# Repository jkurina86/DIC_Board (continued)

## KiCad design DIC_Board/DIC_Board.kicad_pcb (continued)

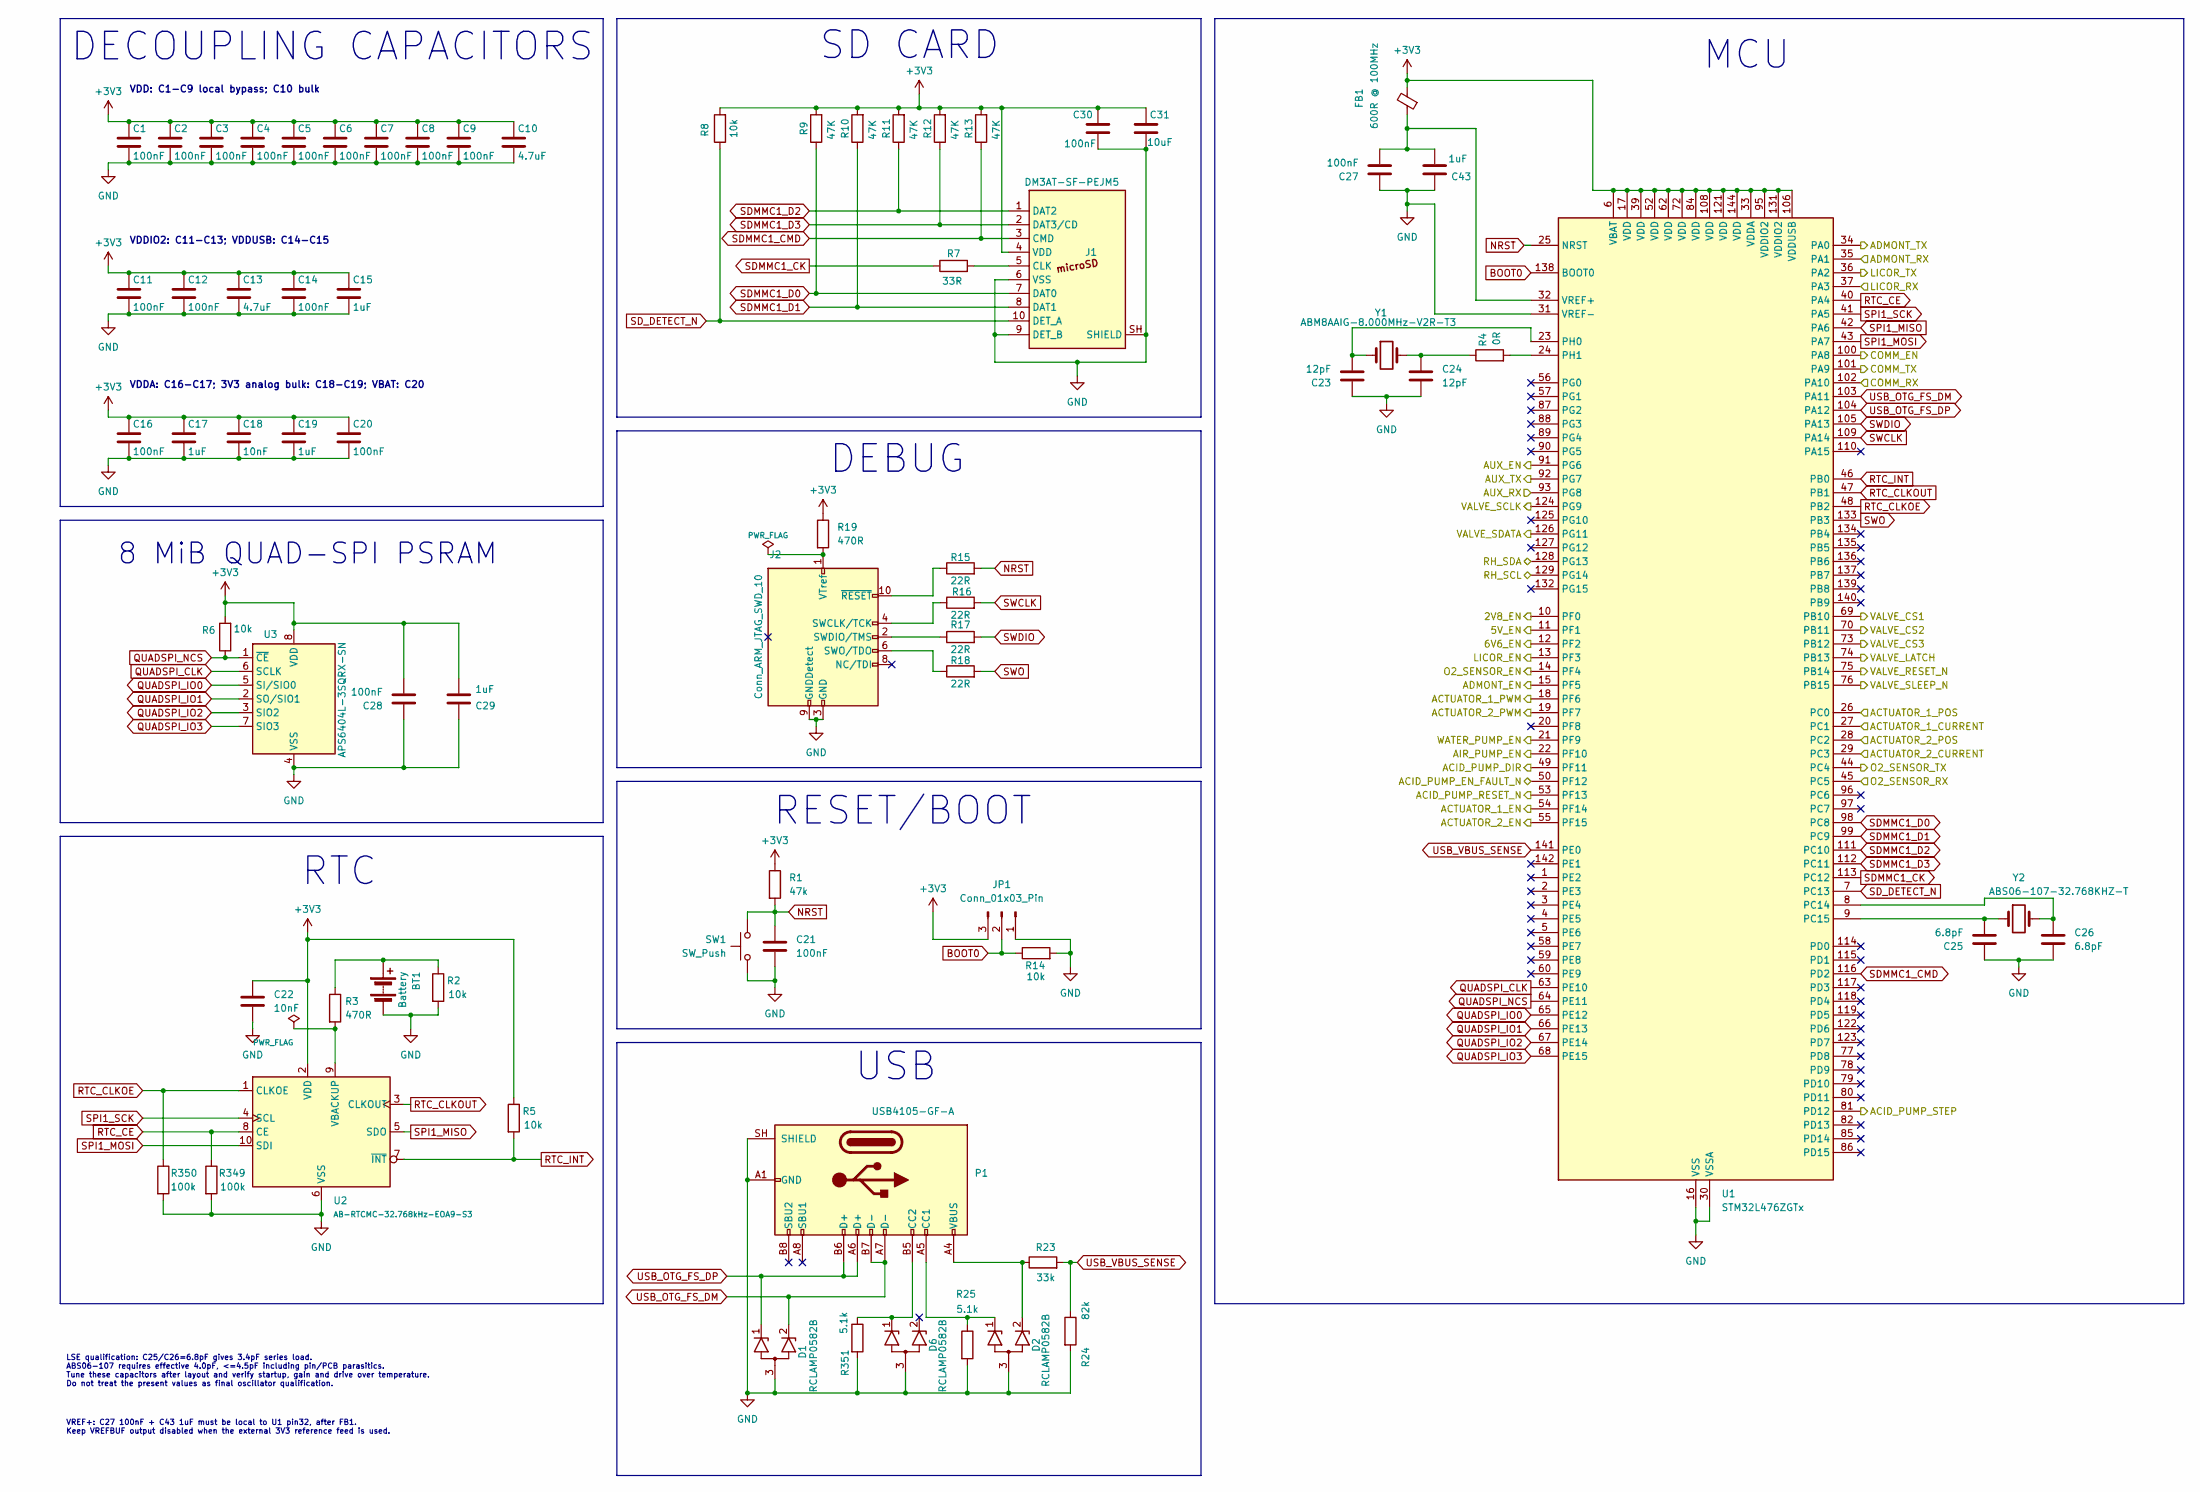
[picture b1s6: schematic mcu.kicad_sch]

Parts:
BT1: Battery; BatteryHolder_Keystone_3013_1x16mm; MPN 3013; DigiKey 36-3013-ND
C1, C2, C3, C4, C5, C6, C7, C8, C9, C11, C12, C14, C16, C20, C21, C27, C28, C30: 100nF; C_0603_1608Metric; Voltage Rating 50V; Tolerance 10%; MPN C1608X7R1H104K080AA
C10, C13: 4.7uF; C_0805_2012Metric; Voltage Rating 25V; Tolerance 10%; MPN C2012X7R1E475K125AB
C15, C17, C19, C29, C43: 1uF; C_0603_1608Metric; Voltage Rating 25V; Tolerance 10%; MPN C1608X7R1E105K080AB
C18, C22: 10nF; C_0603_1608Metric; Voltage Rating 50V; Tolerance 10%; MPN C1608X7R1H103K080AA
C23, C24: 12pF; C_0603_1608Metric; Voltage Rating 50V; Tolerance 5%; MPN C1608C0G1H120J080AA
C25, C26: 6.8pF; C_0402_1005Metric; Voltage Rating 50V; Tolerance 0.25pF; MPN GRM1555C1H6R8CA01D
C31: 10uF; C_0805_2012Metric; Voltage Rating 16V; Tolerance 10%; MPN C2012X7S1C106K125AC
D1, D2, D6: RCLAMP0582B; SOT-523; MPN RClamp0582B.TCT
FB1: 600R @ 100MHz; L_0603_1608Metric; Current Rating 500mA; MPN BLM18AG601SN1D
J1: DM3AT-SF-PEJM5; microSD_HC_Hirose_DM3AT-SF-PEJM5; MPN DM3AT-SF-PEJM5
J2: Conn_ARM_JTAG_SWD_10; Wurth_61201021621_2x05_P2.54mm_Vertical; MPN 61201021621; DigiKey 732-2094-ND
JP1: Conn_01x03_Pin; PinHeader_Wurth_61300311121_1x03_P2.54mm_Vertical; MPN 61300311121
P1: USB4105-GF-A; USB_C_Receptacle_GCT_USB4105-xx-A_16P_TopMnt_Horizontal; MPN USB4105-GF-A; DigiKey 2073-USB4105-GF-ACT-ND
R1: 47k; R_0603_1608Metric; Tolerance 1%; Power Rating 0.125W; MPN CRCW060347K0FKEA
R2, R5, R6, R8, R14: 10k; R_0603_1608Metric; Tolerance 1%; Power Rating 0.125W; MPN CRCW060310K0FKEA
R3, R19: 470R; R_0603_1608Metric; Tolerance 1%; Power Rating 0.125W; MPN CRCW0603470RFKEA
R4: 0R; R_0603_1608Metric; Tolerance Jumper; Power Rating 0.125W; MPN CRCW06030000Z0EA
R7: 33R; R_0603_1608Metric; Tolerance 1%; Power Rating 0.125W; MPN CRCW060333R0FKEA
R9, R10, R11, R12, R13: 47K; R_0603_1608Metric; Tolerance 1%; Power Rating 0.125W; MPN CRCW060347K0FKEA
R15, R16, R17, R18: 22R; R_0603_1608Metric; Tolerance 1%; Power Rating 0.125W; MPN CRCW060322R0FKEA
R23: 33k; R_0402_1005Metric; Tolerance 1%; Power Rating 0.1W; MPN CRCW040233K0FKED
R24: 82k; R_0402_1005Metric; Tolerance 1%; Power Rating 0.1W; MPN CRCW040282K0FKED
R25, R351: 5.1k; R_0402_1005Metric; Tolerance 1%; Power Rating 0.1W; MPN CRCW04025K10FKED
R349, R350: 100k; R_0603_1608Metric; Tolerance 1%; Power Rating 0.125W; MPN CRCW0603100KFKEA
SW1: SW_Push; SW_ESwitch_TL6330AF200Q; MPN TL6330AF200Q
U1: STM32L476ZGTx; LQFP-144_20x20mm_P0.5mm; MPN STM32L476ZGT6
U2: AB-RTCMC-32.768kHz-EOA9-S3; RTC_SMD_MicroCrystal_C3_2.5x3.7mm; MPN AB-RTCMC-32.768kHz-EOA9-S3
U3: APS6404L-3SQRX-SN; SOIC-8_3.9x4.9mm_P1.27mm; MPN APS6404L-3SQRX-SN; Mouser 878-APS6404L-3SQRXSN
Y1: ABM8AAIG-8.000MHz-V2R-T3; ABM8AAIG-2Pin_3.2x2.5mm; MPN ABM8AAIG-8.000MHz-V2R-T3
Y2: ABS06-107-32.768KHZ-T; ABS06-107-2Pin_2.0x1.2mm; MPN ABS06-107-32.768KHZ-T

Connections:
+3V3: C1.1, C2.1, C3.1, C4.1, C5.1, C6.1, C7.1, C8.1, C9.1, C10.1, C11.1, C12.1, C13.1, C14.1, C15.1, C16.1, C17.1, C18.1, C19.1, C20.1, C22.2, C28.1, C29.1, C30.1, C31.1, FB1.2, J1.4 (VDD), JP1.3, R1.1, R5.1, R6.2, R8.2, R9.2, R10.2, R11.2, R12.2, R13.2, R19.1, U1.6 (VBAT), U1.17 (VDD), U1.33 (VDDA), U1.39 (VDD), U1.52 (VDD), U1.62 (VDD), U1.72 (VDD), U1.84 (VDD), U1.95 (VDDIO2), U1.106 (VDDUSB), U1.108 (VDD), U1.121 (VDD), U1.131 (VDDIO2), U1.144 (VDD), U2.2 (VDD), U3.8 (VDD); also elsewhere on the board
/Actuators/ACTUATOR_1_CURRENT: U1.27 (PC1); also elsewhere on the board
/Actuators/ACTUATOR_1_EN: U1.54 (PF14); also elsewhere on the board
/Actuators/ACTUATOR_1_POS: U1.26 (PC0); also elsewhere on the board
/Actuators/ACTUATOR_1_PWM: U1.18 (PF6); also elsewhere on the board
/Actuators/ACTUATOR_2_CURRENT: U1.29 (PC3); also elsewhere on the board
/Actuators/ACTUATOR_2_EN: U1.55 (PF15); also elsewhere on the board
/Actuators/ACTUATOR_2_POS: U1.28 (PC2); also elsewhere on the board
/Actuators/ACTUATOR_2_PWM: U1.19 (PF7); also elsewhere on the board
/Comms/AUX_EN: U1.91 (PG6); also elsewhere on the board
/Comms/AUX_RX: U1.93 (PG8); also elsewhere on the board
/Comms/AUX_TX: U1.92 (PG7); also elsewhere on the board
/Comms/COMM_EN: U1.100 (PA8); also elsewhere on the board
/Comms/COMM_RX: U1.102 (PA10); also elsewhere on the board
/Comms/COMM_TX: U1.101 (PA9); also elsewhere on the board
/Power/2V8_EN: U1.10 (PF0); also elsewhere on the board
/Power/5V_EN: U1.11 (PF1); also elsewhere on the board
/Power/6V6_EN: U1.12 (PF2); also elsewhere on the board
/Pump Control/ACID_PUMP_DIR: U1.49 (PF11); also elsewhere on the board
/Pump Control/ACID_PUMP_EN_FAULT_N: U1.50 (PF12); also elsewhere on the board
/Pump Control/ACID_PUMP_RESET_N: U1.53 (PF13); also elsewhere on the board
/Pump Control/ACID_PUMP_STEP: U1.81 (PD12); also elsewhere on the board
/Pump Control/AIR_PUMP_EN: U1.22 (PF10); also elsewhere on the board
/Pump Control/WATER_PUMP_EN: U1.21 (PF9); also elsewhere on the board
/STM32 MCU/ADMONT_EN: U1.15 (PF5); also elsewhere on the board
/STM32 MCU/ADMONT_RX: U1.35 (PA1); also elsewhere on the board
/STM32 MCU/ADMONT_TX: U1.34 (PA0); also elsewhere on the board
/STM32 MCU/LICOR_EN: U1.13 (PF3); also elsewhere on the board
/STM32 MCU/LICOR_RX: U1.37 (PA3); also elsewhere on the board
/STM32 MCU/LICOR_TX: U1.36 (PA2); also elsewhere on the board
/STM32 MCU/O2_SENSOR_EN: U1.14 (PF4); also elsewhere on the board
/STM32 MCU/O2_SENSOR_RX: U1.45 (PC5); also elsewhere on the board
/STM32 MCU/O2_SENSOR_TX: U1.44 (PC4); also elsewhere on the board
/STM32 MCU/RH_SCL: U1.129 (PG14); also elsewhere on the board
/STM32 MCU/RH_SDA: U1.128 (PG13); also elsewhere on the board
/Valve Control/VALVE_CS1: U1.69 (PB10); also elsewhere on the board
/Valve Control/VALVE_CS2: U1.70 (PB11); also elsewhere on the board
/Valve Control/VALVE_CS3: U1.73 (PB12); also elsewhere on the board
/Valve Control/VALVE_LATCH: U1.74 (PB13); also elsewhere on the board
/Valve Control/VALVE_RESET_N: U1.75 (PB14); also elsewhere on the board
/Valve Control/VALVE_SCLK: U1.124 (PG9); also elsewhere on the board
/Valve Control/VALVE_SDATA: U1.126 (PG11); also elsewhere on the board
/Valve Control/VALVE_SLEEP_N: U1.76 (PB15); also elsewhere on the board
BOOT0: JP1.2, R14.1, U1.138 (BOOT0)
GND: BT1.2 (-), C1.2, C2.2, C3.2, C4.2, C5.2, C6.2, C7.2, C8.2, C9.2, C10.2, C11.2, C12.2, C13.2, C14.2, C15.2, C16.2, C17.2, C18.2, C19.2, C20.2, C21.1, C22.1, C23.2, C24.1, C25.2, C26.1, C27.2, C28.2, C29.2, C30.2, C31.2, C43.2, D1.3 (A), D2.3 (A), D6.3 (A), J1.6 (VSS), J1.9 (DET_B), J1.SH (SHIELD), J2.3 (GND), J2.5 (GND), J2.9 (GNDDetect), JP1.1, P1.A1 (GND), P1.A12 (GND), P1.B1 (GND), P1.B12 (GND), P1.SH (SHIELD), R2.2, R14.2, R24.2, R25.2, R349.2, R350.2, R351.2, SW1.2, U1.16 (VSS), U1.30 (VSSA), U1.31 (VREF-), U1.38 (VSS), U1.51 (VSS), U1.61 (VSS), U1.71 (VSS), U1.83 (VSS), U1.94 (VSS), U1.107 (VSS), U1.120 (VSS), U1.130 (VSS), U1.143 (VSS), U2.6 (VSS), U3.4 (VSS); also elsewhere on the board
NRST: C21.2, R1.2, R15.2, SW1.1, U1.25 (NRST)
unnamed: BT1.1 (+), R2.1, R3.1
unnamed: C24.2, R4.1, Y1.2
unnamed: D2.1 (K1), P1.A5 (CC1), R25.1
unnamed: D2.2 (K2), P1.A4 (VBUS), P1.A9 (VBUS), P1.B4 (VBUS), P1.B9 (VBUS), R23.1
unnamed: D6.1 (K1), P1.B5 (CC2), R351.1
unnamed: J1.5 (CLK), R7.2
unnamed: J2.4 (SWCLK/TCK), R16.1
unnamed: J2.2 (SWDIO/TMS), R17.1
unnamed: J2.6 (SWO/TDO), R18.1
unnamed: J2.1 (VTref), R19.2
unnamed: J2.10 (~RESET), R15.1
unnamed: C26.2, U1.8 (PC14), Y2.2
unnamed: C25.1, U1.9 (PC15), Y2.1
unnamed: C23.1, U1.23 (PH0), Y1.1
unnamed: R4.2, U1.24 (PH1)
unnamed: C27.1, C43.1, FB1.1, U1.32 (VREF+)
unnamed: R3.2, U2.9 (VBACKUP)
QUADSPI_CLK: U1.63 (PE10), U3.6 (SCLK)
QUADSPI_IO0: U1.65 (PE12), U3.5 (SI/SIO0)
QUADSPI_IO1: U1.66 (PE13), U3.2 (SO/SIO1)
QUADSPI_IO2: U1.67 (PE14), U3.3 (SIO2)
QUADSPI_IO3: U1.68 (PE15), U3.7 (SIO3)
QUADSPI_NCS: R6.1, U1.64 (PE11), U3.1 (~CE)
RTC_CE: R349.1, U1.40 (PA4), U2.8 (CE)
RTC_CLKOE: R350.1, U1.48 (PB2), U2.1 (CLKOE)
RTC_CLKOUT: U1.47 (PB1), U2.3 (CLKOUT)
RTC_INT: R5.2, U1.46 (PB0), U2.7 (~INT)
SDMMC1_CK: R7.1, U1.113 (PC12)
SDMMC1_CMD: J1.3 (CMD), R13.1, U1.116 (PD2)
SDMMC1_D0: J1.7 (DAT0), R9.1, U1.98 (PC8)
SDMMC1_D1: J1.8 (DAT1), R10.1, U1.99 (PC9)
SDMMC1_D2: J1.1 (DAT2), R11.1, U1.111 (PC10)
SDMMC1_D3: J1.2 (DAT3/CD), R12.1, U1.112 (PC11)
SD_DETECT_N: J1.10 (DET_A), R8.1, U1.7 (PC13)
SPI1_MISO: U1.42 (PA6), U2.5 (SDO)
SPI1_MOSI: U1.43 (PA7), U2.10 (SDI)
SPI1_SCK: U1.41 (PA5), U2.4 (SCL)
SWCLK: R16.2, U1.109 (PA14)
SWDIO: R17.2, U1.105 (PA13)
SWO: R18.2, U1.133 (PB3)
USB_OTG_FS_DM: D1.2 (K2), P1.A7 (D-), P1.B7 (D-), U1.103 (PA11)
USB_OTG_FS_DP: D1.1 (K1), P1.A6 (D+), P1.B6 (D+), U1.104 (PA12)
USB_VBUS_SENSE: R23.2, R24.1, U1.141 (PE0)

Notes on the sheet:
DECOUPLING CAPACITORS
RTC
USB
DEBUG
8 MiB QUAD-SPI PSRAM
VREF+: C27 100nF + C43 1uF must be local to U1 pin32, after FB1. Keep VREFBUF output disabled when the external 3V3 reference feed is used.
MCU
VDD: C1-C9 local bypass; C10 bulk
VDDIO2: C11-C13; VDDUSB: C14-C15
VDDA: C16-C17; 3V3 analog bulk: C18-C19; VBAT: C20
RESET/BOOT
SD CARD
LSE qualification: C25/C26=6.8pF gives 3.4pF series load. ABS06-107 requires effective 4.0pF, <=4.5pF including pin/PCB parasitics. Tune these capacitors after layout and verify startup, gain and drive over temperature. Do not treat the present values as final oscillator qualification.

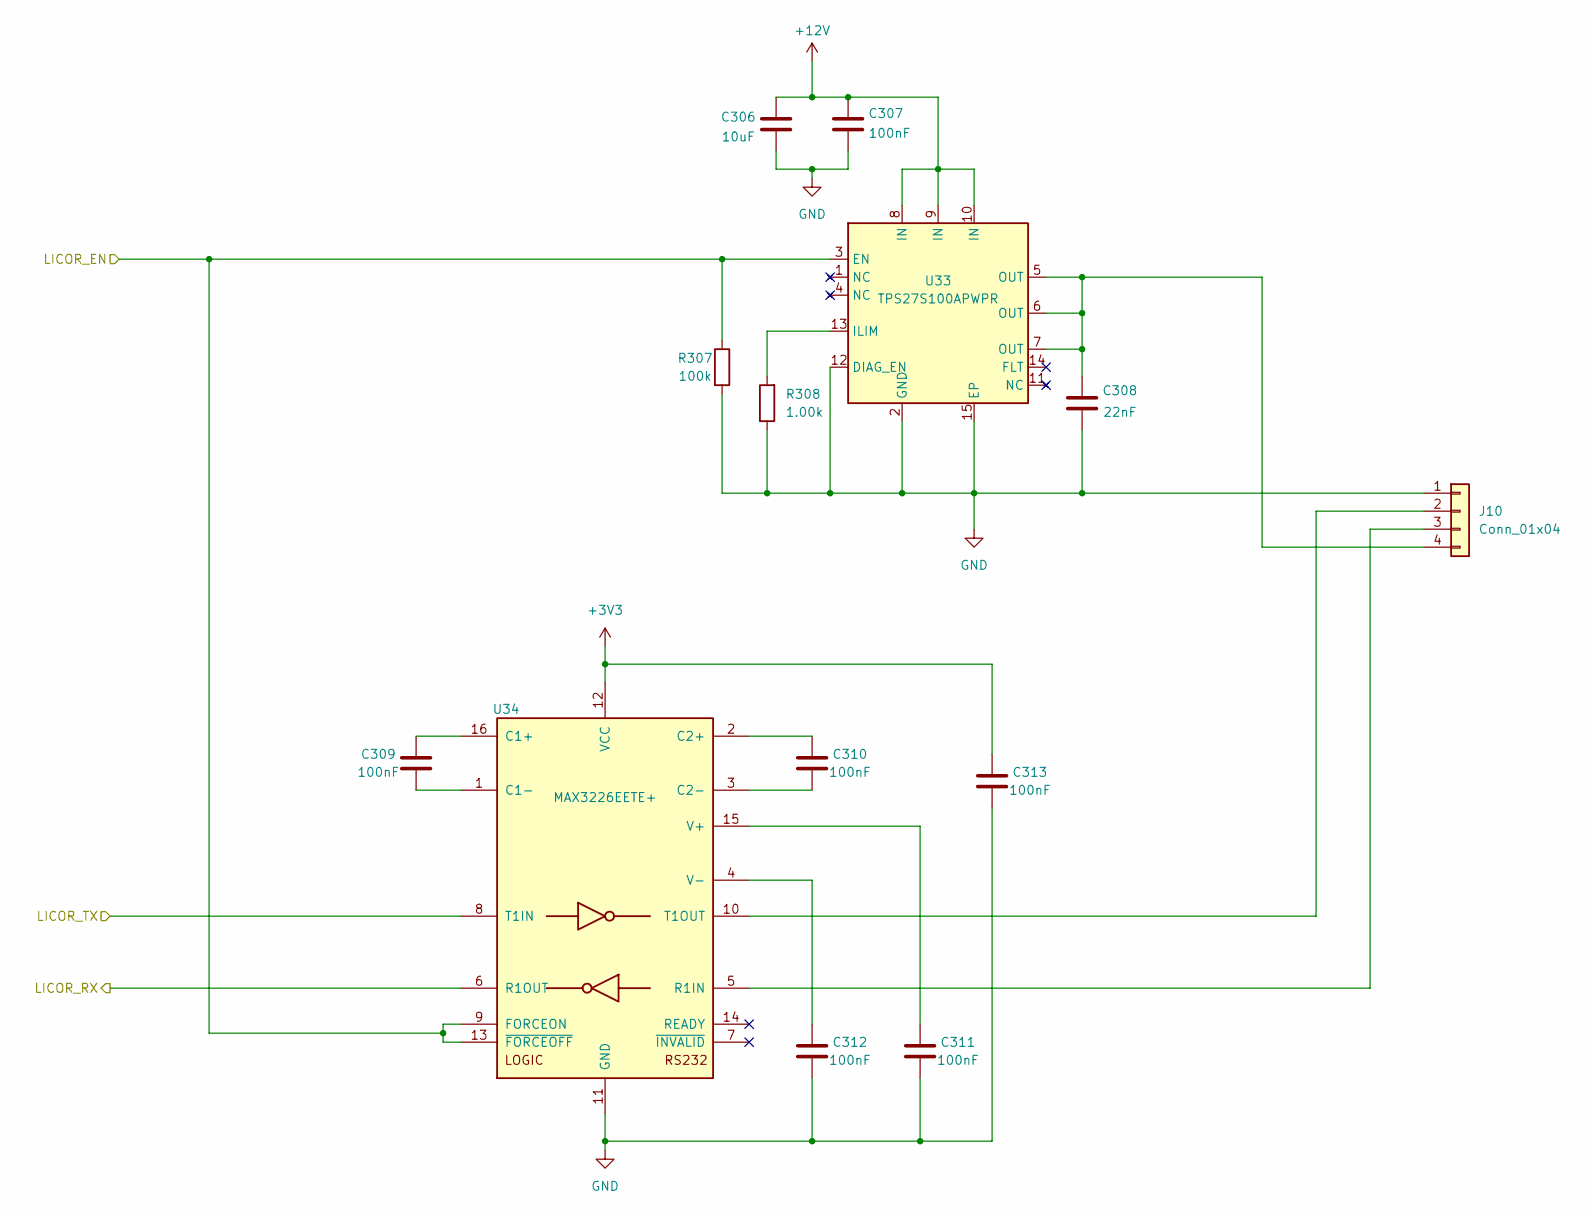
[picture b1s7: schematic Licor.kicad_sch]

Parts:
C306: 10uF; C_1206_3216Metric; MPN CGA5L1X7R1H106K160AC
C307, C309, C310, C311, C312, C313: 100nF; C_0402_1005Metric; MPN GRM155R71H104ME14D
C308: 22nF; C_0402_1005Metric; MPN GRM155R71H223KA12D
J10: Conn_01x04; Molex_Micro-Fit_3.0_43045-0400_2x02_P3.00mm_Horizontal; MPN 0430450400
R307: 100k; R_0402_1005Metric; MPN CRCW0402100KFKED
R308: 1.00k; R_0402_1005Metric; MPN CRCW04021K00FKED
U33: TPS27S100APWPR; TPS27S100_Thermal_Drill0p3; MPN TPS27S100APWPR; DigiKey 296-49002-1-ND
U34: MAX3226EETE+; TQFN-16-1EP_5x5mm_P0.8mm_EP3.1x3.1mm; MPN MAX3226EETE+

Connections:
+3V3: C313.1, U34.12 (VCC); also elsewhere on the board
+12V: C306.1, C307.1, U33.8 (IN), U33.9 (IN), U33.10 (IN); also elsewhere on the board
/STM32 MCU/LICOR_EN: R307.1, U33.3 (EN), U34.9 (FORCEON), U34.13 (~FORCEOFF); also elsewhere on the board
/STM32 MCU/LICOR_RX: U34.6 (R1OUT); also elsewhere on the board
/STM32 MCU/LICOR_TX: U34.8 (T1IN); also elsewhere on the board
GND: C306.2, C307.2, C308.2, C311.2, C312.2, C313.2, J10.1, R307.2, R308.1, U33.2 (GND), U33.12 (DIAG_EN), U33.15 (EP), U34.11 (GND), U34.17 (EP); also elsewhere on the board
unnamed: J10.2, U34.10 (T1OUT)
unnamed: J10.3, U34.5 (R1IN)
unnamed: C308.1, J10.4, U33.5 (OUT), U33.6 (OUT), U33.7 (OUT)
unnamed: R308.2, U33.13 (ILIM)
unnamed: C309.1, U34.16 (C1+)
unnamed: C309.2, U34.1 (C1-)
unnamed: C310.1, U34.2 (C2+)
unnamed: C310.2, U34.3 (C2-)
unnamed: C311.1, U34.15 (V+)
unnamed: C312.1, U34.4 (V-)

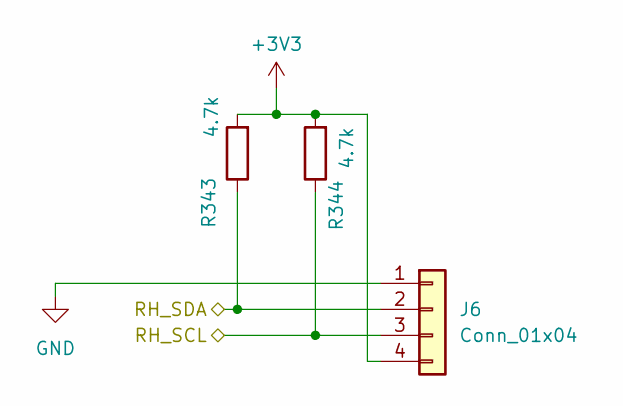
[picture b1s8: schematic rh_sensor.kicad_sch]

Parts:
J6: Conn_01x04; Molex_Micro-Fit_3.0_43045-0400_2x02_P3.00mm_Horizontal; MPN 0430450400
R343, R344: 4.7k; R_0603_1608Metric; Tolerance 1%; Power Rating 0.125W; MPN CRCW06034K70FKEA

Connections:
+3V3: J6.4, R343.2, R344.2; also elsewhere on the board
/STM32 MCU/RH_SCL: J6.3, R344.1; also elsewhere on the board
/STM32 MCU/RH_SDA: J6.2, R343.1; also elsewhere on the board
GND: J6.1; also elsewhere on the board

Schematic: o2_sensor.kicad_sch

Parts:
C328: 10uF; C_1206_3216Metric; MPN CGA5L1X7R1H106K160AC
C329: 100nF; C_0402_1005Metric; MPN GRM155R71H104ME14D
C330: 22nF; C_0402_1005Metric; MPN GRM155R71H223KA12D
J7: Conn_01x04; Molex_Micro-Fit_3.0_43045-0400_2x02_P3.00mm_Horizontal; MPN 0430450400
R340: 15k; R_0402_1005Metric; MPN CRCW040215K0FKED
R341: 100k; R_0402_1005Metric; MPN CRCW0402100KFKED
R342: 1.00k; R_0402_1005Metric; MPN CRCW04021K00FKED
U38: TPS27S100APWPR; TPS27S100_Thermal_Drill0p3; MPN TPS27S100APWPR; DigiKey 296-49002-1-ND

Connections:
+5V: C328.1, C329.1, U38.8 (IN), U38.9 (IN), U38.10 (IN); also elsewhere on the board
/STM32 MCU/O2_SENSOR_EN: R340.1; also elsewhere on the board
/STM32 MCU/O2_SENSOR_RX: J7.3; also elsewhere on the board
/STM32 MCU/O2_SENSOR_TX: J7.2; also elsewhere on the board
GND: C328.2, C329.2, C330.2, J7.1, R341.2, R342.1, U38.2 (GND), U38.12 (DIAG_EN), U38.15 (EP); also elsewhere on the board
unnamed: C330.1, J7.4, U38.5 (OUT), U38.6 (OUT), U38.7 (OUT)
unnamed: R340.2, R341.1, U38.3 (EN)
unnamed: R342.2, U38.13 (ILIM)

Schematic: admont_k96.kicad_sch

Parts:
C314: 10uF; C_1206_3216Metric; MPN CGA5L1X7R1H106K160AC
C315: 100nF; C_0402_1005Metric; MPN GRM155R71H104ME14D
C316: 22nF; C_0402_1005Metric; MPN GRM155R71H223KA12D
J8: Conn_01x04; Molex_Micro-Fit_3.0_43045-0400_2x02_P3.00mm_Horizontal; MPN 0430450400
R309: 15k; R_0402_1005Metric; MPN CRCW040215K0FKED
R310: 100k; R_0402_1005Metric; MPN CRCW0402100KFKED
R311: 1.00k; R_0402_1005Metric; MPN CRCW04021K00FKED
U35: TPS27S100APWPR; TPS27S100_Thermal_Drill0p3; MPN TPS27S100APWPR; DigiKey 296-49002-1-ND

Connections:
+6V6: C314.1, C315.1, U35.8 (IN), U35.9 (IN), U35.10 (IN); also elsewhere on the board
/STM32 MCU/ADMONT_EN: R309.1; also elsewhere on the board
/STM32 MCU/ADMONT_RX: J8.3; also elsewhere on the board
/STM32 MCU/ADMONT_TX: J8.2; also elsewhere on the board
GND: C314.2, C315.2, C316.2, J8.1, R310.2, R311.1, U35.2 (GND), U35.12 (DIAG_EN), U35.15 (EP); also elsewhere on the board
unnamed: C316.1, J8.4, U35.5 (OUT), U35.6 (OUT), U35.7 (OUT)
unnamed: R309.2, R310.1, U35.3 (EN)
unnamed: R311.2, U35.13 (ILIM)

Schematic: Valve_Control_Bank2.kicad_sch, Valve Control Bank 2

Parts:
C210: 0.47uF; C_0603_1608Metric_Pad1.08x0.95mm_HandSolder; MPN CGA3E3X7R1H474K080AE
C211: 0.01uF; C_0603_1608Metric_Pad1.08x0.95mm_HandSolder; MPN C0603C103K2RACTU
C212, C213: 0.1uF; C_0603_1608Metric_Pad1.08x0.95mm_HandSolder; MPN C0603X104K5RAC7867
C214: 100uF; CP_Radial_D8.0mm_P3.50mm; MPN UHE1H101MPD
R332, R333, R334, R335: 3.3R; R_0402_1005Metric; Tolerance 1%; Power Rating 0.2W; MPN CRCW04023R30FKEDHP
U21: DRV8823QDCARQ1; DRV8823_DCA48_ReviewFixed; MPN DRV8823QDCARQ1

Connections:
+12V: C212.1, C213.2, C214.1, U21.1 (VM1), U21.2 (VM2), U21.23 (VM3), U21.24 (VM4); also elsewhere on the board
/Valve Control/VALVE_CS2: U21.45 (SCS); also elsewhere on the board
/Valve Control/VALVE_LATCH: U21.30 (SSTB); also elsewhere on the board
/Valve Control/VALVE_RESET_N: U21.43 (RESETn); also elsewhere on the board
/Valve Control/VALVE_SCLK: U21.33 (SCLK); also elsewhere on the board
/Valve Control/VALVE_SDATA: U21.31 (SDATA); also elsewhere on the board
/Valve Control/VALVE_SLEEP_N: U21.42 (SLEEPn); also elsewhere on the board
/Valve Control/Valve Control Bank 2/VALVE5_A: U21.5 (AOUT1); also elsewhere on the board
/Valve Control/Valve Control Bank 2/VALVE5_B: U21.3 (AOUT2); also elsewhere on the board
/Valve Control/Valve Control Bank 2/VALVE6_A: U21.48 (BOUT1); also elsewhere on the board
/Valve Control/Valve Control Bank 2/VALVE6_B: U21.46 (BOUT2); also elsewhere on the board
/Valve Control/Valve Control Bank 2/VALVE7_A: U21.27 (COUT1); also elsewhere on the board
/Valve Control/Valve Control Bank 2/VALVE7_B: U21.25 (COUT2); also elsewhere on the board
/Valve Control/Valve Control Bank 2/VALVE8_A: U21.22 (DOUT1); also elsewhere on the board
/Valve Control/Valve Control Bank 2/VALVE8_B: U21.20 (DOUT2); also elsewhere on the board
/Valve Control/Valve Control Bank 2/VREF1: C210.2, U21.16 (V3P3), U21.17 (ABVREF), U21.18 (CDVREF)
GND: C210.1, C213.1, C214.2, R332.2, R333.2, R334.2, R335.2, U21.10 (PGND), U21.11 (PGND), U21.12 (PGND), U21.13 (PGND), U21.14 (PGND), U21.15 (PGND), U21.34 (PGND), U21.35 (PGND), U21.36 (PGND), U21.37 (PGND), U21.38 (PGND), U21.39 (PGND), U21.49 (EPAD); also elsewhere on the board
unnamed: R332.1, U21.4 (AISEN)
unnamed: R333.1, U21.47 (BISEN)
unnamed: R334.1, U21.26 (CISEN)
unnamed: C211.2, U21.7 (CP1)
unnamed: C211.1, U21.8 (CP2)
unnamed: R335.1, U21.21 (DISEN)
unnamed: C212.2, U21.9 (VCP)

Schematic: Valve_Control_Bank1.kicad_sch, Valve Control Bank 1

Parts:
C200: 0.47uF; C_0603_1608Metric_Pad1.08x0.95mm_HandSolder; MPN CGA3E3X7R1H474K080AE
C201: 0.01uF; C_0603_1608Metric_Pad1.08x0.95mm_HandSolder; MPN C0603C103K2RACTU
C202, C203: 0.1uF; C_0603_1608Metric_Pad1.08x0.95mm_HandSolder; MPN C0603X104K5RAC7867
C204: 100uF; CP_Radial_D8.0mm_P3.50mm; MPN UHE1H101MPD
R318, R319, R330, R331: 3.3R; R_0402_1005Metric; Tolerance 1%; Power Rating 0.2W; MPN CRCW04023R30FKEDHP
U20: DRV8823QDCARQ1; DRV8823_DCA48_ReviewFixed; MPN DRV8823QDCARQ1

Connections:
+12V: C202.1, C203.2, C204.1, U20.1 (VM1), U20.2 (VM2), U20.23 (VM3), U20.24 (VM4); also elsewhere on the board
/Valve Control/VALVE_CS1: U20.45 (SCS); also elsewhere on the board
/Valve Control/VALVE_LATCH: U20.30 (SSTB); also elsewhere on the board
/Valve Control/VALVE_RESET_N: U20.43 (RESETn); also elsewhere on the board
/Valve Control/VALVE_SCLK: U20.33 (SCLK); also elsewhere on the board
/Valve Control/VALVE_SDATA: U20.31 (SDATA); also elsewhere on the board
/Valve Control/VALVE_SLEEP_N: U20.42 (SLEEPn); also elsewhere on the board
/Valve Control/Valve Control Bank 1/VALVE1_A: U20.5 (AOUT1); also elsewhere on the board
/Valve Control/Valve Control Bank 1/VALVE1_B: U20.3 (AOUT2); also elsewhere on the board
/Valve Control/Valve Control Bank 1/VALVE2_A: U20.48 (BOUT1); also elsewhere on the board
/Valve Control/Valve Control Bank 1/VALVE2_B: U20.46 (BOUT2); also elsewhere on the board
/Valve Control/Valve Control Bank 1/VALVE3_A: U20.27 (COUT1); also elsewhere on the board
/Valve Control/Valve Control Bank 1/VALVE3_B: U20.25 (COUT2); also elsewhere on the board
/Valve Control/Valve Control Bank 1/VALVE4_A: U20.22 (DOUT1); also elsewhere on the board
/Valve Control/Valve Control Bank 1/VALVE4_B: U20.20 (DOUT2); also elsewhere on the board
/Valve Control/Valve Control Bank 1/VREF1: C200.2, U20.16 (V3P3), U20.17 (ABVREF), U20.18 (CDVREF)
GND: C200.1, C203.1, C204.2, R318.2, R319.2, R330.2, R331.2, U20.10 (PGND), U20.11 (PGND), U20.12 (PGND), U20.13 (PGND), U20.14 (PGND), U20.15 (PGND), U20.34 (PGND), U20.35 (PGND), U20.36 (PGND), U20.37 (PGND), U20.38 (PGND), U20.39 (PGND), U20.49 (EPAD); also elsewhere on the board
unnamed: R318.1, U20.4 (AISEN)
unnamed: R319.1, U20.47 (BISEN)
unnamed: R330.1, U20.26 (CISEN)
unnamed: C201.2, U20.7 (CP1)
unnamed: C201.1, U20.8 (CP2)
unnamed: R331.1, U20.21 (DISEN)
unnamed: C202.2, U20.9 (VCP)

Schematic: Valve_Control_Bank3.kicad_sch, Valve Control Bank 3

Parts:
C220: 0.47uF; C_0603_1608Metric_Pad1.08x0.95mm_HandSolder; MPN CGA3E3X7R1H474K080AE
C221: 0.01uF; C_0603_1608Metric_Pad1.08x0.95mm_HandSolder; MPN C0603C103K2RACTU
C222, C223: 0.1uF; C_0603_1608Metric_Pad1.08x0.95mm_HandSolder; MPN C0603X104K5RAC7867
C224: 100uF; CP_Radial_D8.0mm_P3.50mm; MPN UHE1H101MPD
R336, R337, R338, R339: 3.3R; R_0402_1005Metric; Tolerance 1%; Power Rating 0.2W; MPN CRCW04023R30FKEDHP
U22: DRV8823QDCARQ1; DRV8823_DCA48_ReviewFixed; MPN DRV8823QDCARQ1

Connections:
+12V: C222.1, C223.2, C224.1, U22.1 (VM1), U22.2 (VM2), U22.23 (VM3), U22.24 (VM4); also elsewhere on the board
/Valve Control/VALVE_CS3: U22.45 (SCS); also elsewhere on the board
/Valve Control/VALVE_LATCH: U22.30 (SSTB); also elsewhere on the board
/Valve Control/VALVE_RESET_N: U22.43 (RESETn); also elsewhere on the board
/Valve Control/VALVE_SCLK: U22.33 (SCLK); also elsewhere on the board
/Valve Control/VALVE_SDATA: U22.31 (SDATA); also elsewhere on the board
/Valve Control/VALVE_SLEEP_N: U22.42 (SLEEPn); also elsewhere on the board
/Valve Control/Valve Control Bank 3/VALVE9_A: U22.5 (AOUT1); also elsewhere on the board
/Valve Control/Valve Control Bank 3/VALVE9_B: U22.3 (AOUT2); also elsewhere on the board
/Valve Control/Valve Control Bank 3/VALVE10_A: U22.48 (BOUT1); also elsewhere on the board
/Valve Control/Valve Control Bank 3/VALVE10_B: U22.46 (BOUT2); also elsewhere on the board
/Valve Control/Valve Control Bank 3/VALVE11_A: U22.27 (COUT1); also elsewhere on the board
/Valve Control/Valve Control Bank 3/VALVE11_B: U22.25 (COUT2); also elsewhere on the board
/Valve Control/Valve Control Bank 3/VALVE12_A: U22.22 (DOUT1); also elsewhere on the board
/Valve Control/Valve Control Bank 3/VALVE12_B: U22.20 (DOUT2); also elsewhere on the board
/Valve Control/Valve Control Bank 3/VREF1: C220.2, U22.16 (V3P3), U22.17 (ABVREF), U22.18 (CDVREF)
GND: C220.1, C223.1, C224.2, R336.2, R337.2, R338.2, R339.2, U22.10 (PGND), U22.11 (PGND), U22.12 (PGND), U22.13 (PGND), U22.14 (PGND), U22.15 (PGND), U22.34 (PGND), U22.35 (PGND), U22.36 (PGND), U22.37 (PGND), U22.38 (PGND), U22.39 (PGND), U22.49 (EPAD); also elsewhere on the board
unnamed: R336.1, U22.4 (AISEN)
unnamed: R337.1, U22.47 (BISEN)
unnamed: R338.1, U22.26 (CISEN)
unnamed: C221.2, U22.7 (CP1)
unnamed: C221.1, U22.8 (CP2)
unnamed: R339.1, U22.21 (DISEN)
unnamed: C222.2, U22.9 (VCP)

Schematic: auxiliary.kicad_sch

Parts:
C332, C338, C339, C341, C342: 100nF; C_0402_1005Metric; MPN GRM155R71H104ME14D
D5: BZT52C8V2-7-F; D_SOD-123; MPN BZT52C8V2-7-F
J12: Conn_01x04; Molex_Micro-Fit_3.0_43045-0400_2x02_P3.00mm_Horizontal; MPN 0430450400
J13: Conn_01x05_Pin; PinHeader_Wurth_61300511121_1x05_P2.54mm_Vertical; MPN 61300511121
Q1: AO4630; SOIC-8_3.9x4.9mm_P1.27mm; Manufacturer_Part_Number AO4630
R345, R346: 100k; R_0402_1005Metric; MPN CRCW0402100KFKED
R347: 4.7k; R_0402_1005Metric; MPN CRCW04024K70FKED
U40: MAX3226EETE+; TQFN-16-1EP_5x5mm_P0.8mm_EP3.1x3.1mm; MPN MAX3226EETE+

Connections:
+3V3: C342.1, J13.1, U40.12 (VCC); also elsewhere on the board
+5V: J13.3; also elsewhere on the board
+12V: J13.5; also elsewhere on the board
/Comms/AUX_EN: Q1.2 (G1), R346.2, U40.9 (FORCEON), U40.13 (~FORCEOFF); also elsewhere on the board
/Comms/AUX_RX: U40.6 (R1OUT); also elsewhere on the board
/Comms/AUX_TX: U40.8 (T1IN); also elsewhere on the board
GND: C339.2, C341.2, C342.2, J12.1, Q1.1 (S1), R346.1, U40.11 (GND), U40.17 (EP); also elsewhere on the board
unnamed: D5.2 (A), Q1.4 (G2), R345.1, R347.1
unnamed: D5.1 (K), J13.2, J13.4, Q1.3 (S2), R345.2
unnamed: J12.2, U40.10 (T1OUT)
unnamed: J12.3, U40.5 (R1IN)
unnamed: J12.4, Q1.5 (D2_1), Q1.6 (D2_2)
unnamed: Q1.7 (D1_1), Q1.8 (D1_2), R347.2
unnamed: C332.1, U40.16 (C1+)
unnamed: C332.2, U40.1 (C1-)
unnamed: C338.1, U40.2 (C2+)
unnamed: C338.2, U40.3 (C2-)
unnamed: C341.1, U40.15 (V+)
unnamed: C339.1, U40.4 (V-)

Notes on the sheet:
AUX_EN: high = load power and RS-232 TX enabled. Wait for peripheral startup before transmitting. U40 exposed pad 17 is connected to GND.

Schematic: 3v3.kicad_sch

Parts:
C34, C35: 0.1uF; C_0603_1608Metric; Voltage Rating 50V; Tolerance 10%; MPN C1608X7R1H104K080AA
C115, C116: 10uF; C_1206_3216Metric; MPN CGA5L1X7R1H106K160AC
C117, C118: 47uF; C_1210_3225Metric; MPN GRM32ER61A476ME20L
C901: 180uF 16V; CP_Elec_6.3x5.9; Voltage Rating 16V; Tolerance 20%; MPN 16SVPF180M
R109: 10k; R_0402_1005Metric; MPN CRCW040210K0FKED
R110: 4.32k; R_0402_1005Metric; MPN CRCW04024K32FKED
TP23: +3V3; TestPoint_Pad_D1.0mm
U11: TPSM53603RDAR; Texas_B3QFN-14-1EP_5x5.5mm_P0.65mm_ThermalVia; MPN TPSM53603RDAR

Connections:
+3V3: C34.1, C117.1, C118.1, C901.1, R109.1, TP23.1 (1_1), U11.7 (VOUT), U11.8 (VOUT); also elsewhere on the board
/Power/12V/P_IN: C35.1, C115.1, C116.1, U11.1 (VIN), U11.2 (EN), U11.14 (VIN); also elsewhere on the board
GND: C34.2, C35.2, C115.2, C116.2, C117.2, C118.2, C901.2, R110.2, U11.3 (NC/PGND), U11.10 (NC/PGND), U11.11 (NC/PGND), U11.12 (AGND), U11.15 (PGND); also elsewhere on the board
unnamed: R109.2, R110.1, U11.9 (FB)

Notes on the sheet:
Output bulk
REGULATED +3V3 / 3 A

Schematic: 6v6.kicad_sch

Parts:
C32, C33: 0.1uF; C_0603_1608Metric; Voltage Rating 50V; Tolerance 10%; MPN C1608X7R1H104K080AA
C126, C127: 10uF; C_1206_3216Metric; MPN CGA5L1X7R1H106K160AC
C128, C129: 47uF; C_1210_3225Metric; MPN GRM32ER61A476ME20L
C903: 180uF 16V; CP_Elec_6.3x5.9; Voltage Rating 16V; Tolerance 20%; MPN 16SVPF180M
R22: 100k; R_0402_1005Metric; MPN CRCW0402100KFKED
R119: 10k; R_0402_1005Metric; MPN CRCW040210K0FKED
R120: 1.78k; R_0402_1005Metric; MPN CRCW04021K78FKED
TP25: +6V6; TestPoint_Pad_D1.0mm
U13: TPSM53603RDAR; Texas_B3QFN-14-1EP_5x5.5mm_P0.65mm_ThermalVia; MPN TPSM53603RDAR

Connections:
+6V6: C33.1, C128.1, C129.1, C903.1, R119.1, TP25.1 (1_1), U13.7 (VOUT), U13.8 (VOUT); also elsewhere on the board
+12V: C32.1, C126.1, C127.1, U13.1 (VIN), U13.14 (VIN); also elsewhere on the board
/Power/6V6_EN: R22.1, U13.2 (EN); also elsewhere on the board
GND: C32.2, C33.2, C126.2, C127.2, C128.2, C129.2, C903.2, R22.2, R120.2, U13.3 (NC/PGND), U13.10 (NC/PGND), U13.11 (NC/PGND), U13.12 (AGND), U13.15 (PGND); also elsewhere on the board
unnamed: R119.2, R120.1, U13.9 (FB)

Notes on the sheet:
REGULATED +6V6 / 3 A
Output bulk

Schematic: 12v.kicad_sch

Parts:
C40, C42: 0.1uF; C_0603_1608Metric; Voltage Rating 50V; Tolerance 10%; MPN C1608X7R1H104K080AA
C41: 100uF; CP_Elec_8x10.5; Voltage Rating 35V; MPN EEHZA1V101P
C102, C103: 100nF; C_0402_1005Metric; MPN GRM155R71H104ME14D
C104: 100nF; C_0603_1608Metric; Tolerance 10%; Voltage Rating 50V; MPN C1608X7R1H104K080AA
C105: 1nF; C_0603_1608Metric; Tolerance 5%; Voltage Rating 50V; MPN C1608C0G1H102J080AA
C106: 10uF; C_1206_3216Metric; MPN GRM31CR71E106KA12L
C107, C108: 10uF; C_1206_3216Metric; MPN CGA5L1X7R1H106K160AC
C109, C110, C111, C112: 22uF; C_1210_3225Metric; Voltage Rating 25V; Tolerance 20%; MPN GRM32ER71E226ME15L
C113: 220uF; CP_Elec_8x10.5; MPN EEHZA1E221P
C119: 10nF; C_0402_1005Metric; Voltage Rating 50V; Tolerance 10%; MPN CGA2B3X7R1H103K050BB
L10: 4.7uH; L_Coilcraft_XAL1010-XXX; MPN XAL1010-472MEB
R100: 150k; R_0402_1005Metric; MPN CRCW0402150KFKED
R101: 24.9k; R_0402_1005Metric; MPN CRCW040224K9FKED
R102: 49.9k; R_0402_1005Metric; MPN CRCW040249K9FKED
R103: 10m; R_2512_6332Metric; Power Rating 1W; Tolerance 1%; MPN WSL2512R0100FEA
R104: 100k; R_0402_1005Metric; MPN CRCW0402100KFKED
R105: 11.1k; R_0402_1005Metric; MPN CRCW040211K1FKED
R106: 10k; R_0402_1005Metric; Tolerance 1%; MPN CRCW040210K0FKED
R112: 24.9k; R_0402_1005Metric; Tolerance 1%; Power Rating 0.1W; MPN CRCW040224K9FKED
TP22: +12V; TestPoint_Pad_D1.0mm
U10: TPS552892RYQR; Texas_RYQ0021A_TPS552892; MPN TPS552892RYQR

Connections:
+12V: R103.2, R104.1, TP22.1 (1_1), U10.13 (ISN); also elsewhere on the board
/Power/12V/COMP_12V: C105.1, R106.1, U10.15 (COMP)
/Power/12V/DITHER: C119.1, U10.5 (DITH/SYNC)
/Power/12V/EN_UVLO: R100.2, R101.1, U10.1 (EN/UVLO)
/Power/12V/FB_12V: R104.2, R105.1, U10.14 (FB)
/Power/12V/FSW_SET: R102.1, U10.6 (FSW)
/Power/12V/MODE_SEL: R112.1, U10.2 (MODE)
/Power/12V/P_IN: C41.1, C42.1, C107.1, C108.1, R100.1, U10.7 (VIN); also elsewhere on the board
/Power/12V/VCC_BIAS: C106.1, U10.18 (VCC)
/Power/12V/VOUT_RAW: C40.1, C109.1, C110.1, C111.1, C112.1, C113.1, R103.1, U10.11 (VOUT), U10.12 (ISP)
GND: C40.2, C41.2, C42.2, C104.2, C105.2, C106.2, C107.2, C108.2, C109.2, C110.2, C111.2, C112.2, C113.2, C119.2, R101.2, R102.2, R105.2, R112.2, U10.9 (PGND), U10.17 (AGND); also elsewhere on the board
unnamed: C104.1, R106.2
unnamed: C102.2, U10.20 (BOOT1)
unnamed: C103.2, U10.19 (BOOT2)
unnamed: C102.1, L10.1, U10.8 (SW1)
unnamed: C103.1, L10.2, U10.10 (SW2)

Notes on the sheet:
Startup: keep switched loads and downstream rails OFF until 12 V settles; stagger pump / actuator starts.
Layout: tight input/output ceramic loops; Kelvin R103 sense; ground thermal vias. Validate temperature and load steps.
12 V BUCK-BOOST | TPS552892 | 10-14 V INPUT
C204 / C214 / C224: 100 uF each. Total connected 12 V capacitance: 709 uF nominal, <851 uF at +20%.
R103: 5 A nominal output limit (4.75-5.25 A tolerance); not a continuous-output rating.
MODE pulled low: PFM. EXTVCC open: internal bias. PG / CC unused. UVLO retained: ~8.64 V on / ~7.89 V off.
12.01 V nominal; 3 A continuous design target. 4 A peaks require thermal / transient qualification.

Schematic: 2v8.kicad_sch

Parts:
C36, C37: 0.1uF; C_0603_1608Metric; Voltage Rating 50V; Tolerance 10%; MPN C1608X7R1H104K080AA
C130, C131: 10uF; C_1206_3216Metric; MPN CGA5L1X7R1H106K160AC
C133, C134: 47uF; C_1210_3225Metric; MPN GRM32ER61A476ME20L
C904: 180uF 16V; CP_Elec_6.3x5.9; Voltage Rating 16V; Tolerance 20%; MPN 16SVPF180M
R20: 100k; R_0402_1005Metric; MPN CRCW0402100KFKED
R123: 10k; R_0402_1005Metric; MPN CRCW040210K0FKED
R124: 5.56k; R_0402_1005Metric; MPN CRCW04025K56FKED
TP26: +2V8; TestPoint_Pad_D1.0mm
U14: TPSM53603RDAR; Texas_B3QFN-14-1EP_5x5.5mm_P0.65mm_ThermalVia; MPN TPSM53603RDAR

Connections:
+2V8: C37.1, C133.1, C134.1, C904.1, R123.1, TP26.1 (1_1), U14.7 (VOUT), U14.8 (VOUT); also elsewhere on the board
+12V: C36.1, C130.1, C131.1, U14.1 (VIN), U14.14 (VIN); also elsewhere on the board
/Power/2V8_EN: R20.1, U14.2 (EN); also elsewhere on the board
GND: C36.2, C37.2, C130.2, C131.2, C133.2, C134.2, C904.2, R20.2, R124.2, U14.3 (NC/PGND), U14.10 (NC/PGND), U14.11 (NC/PGND), U14.12 (AGND), U14.15 (PGND); also elsewhere on the board
unnamed: R123.2, R124.1, U14.9 (FB)

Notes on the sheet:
REGULATED +2V8 / 3 A
Output bulk

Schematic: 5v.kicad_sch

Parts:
C38, C39: 0.1uF; C_0603_1608Metric; Voltage Rating 50V; Tolerance 10%; MPN C1608X7R1H104K080AA
C121, C122: 10uF; C_1206_3216Metric; MPN CGA5L1X7R1H106K160AC
C123, C124: 47uF; C_1210_3225Metric; MPN GRM32ER61A476ME20L
C902: 180uF 16V; CP_Elec_6.3x5.9; Voltage Rating 16V; Tolerance 20%; MPN 16SVPF180M
R21: 100k; R_0402_1005Metric; MPN CRCW0402100KFKED
R116: 10k; R_0402_1005Metric; MPN CRCW040210K0FKED
R117: 2.49k; R_0402_1005Metric; MPN CRCW04022K49FKED
TP24: +5V; TestPoint_Pad_D1.0mm
U12: TPSM53603RDAR; Texas_B3QFN-14-1EP_5x5.5mm_P0.65mm_ThermalVia; MPN TPSM53603RDAR

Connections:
+5V: C38.1, C123.1, C124.1, C902.1, R116.1, TP24.1 (1_1), U12.7 (VOUT), U12.8 (VOUT); also elsewhere on the board
+12V: C39.1, C121.1, C122.1, U12.1 (VIN), U12.14 (VIN); also elsewhere on the board
/Power/5V_EN: R21.1, U12.2 (EN); also elsewhere on the board
GND: C38.2, C39.2, C121.2, C122.2, C123.2, C124.2, C902.2, R21.2, R117.2, U12.3 (NC/PGND), U12.10 (NC/PGND), U12.11 (NC/PGND), U12.12 (AGND), U12.15 (PGND); also elsewhere on the board
unnamed: R116.2, R117.1, U12.9 (FB)

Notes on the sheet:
Output bulk
REGULATED +5V / 3 A
